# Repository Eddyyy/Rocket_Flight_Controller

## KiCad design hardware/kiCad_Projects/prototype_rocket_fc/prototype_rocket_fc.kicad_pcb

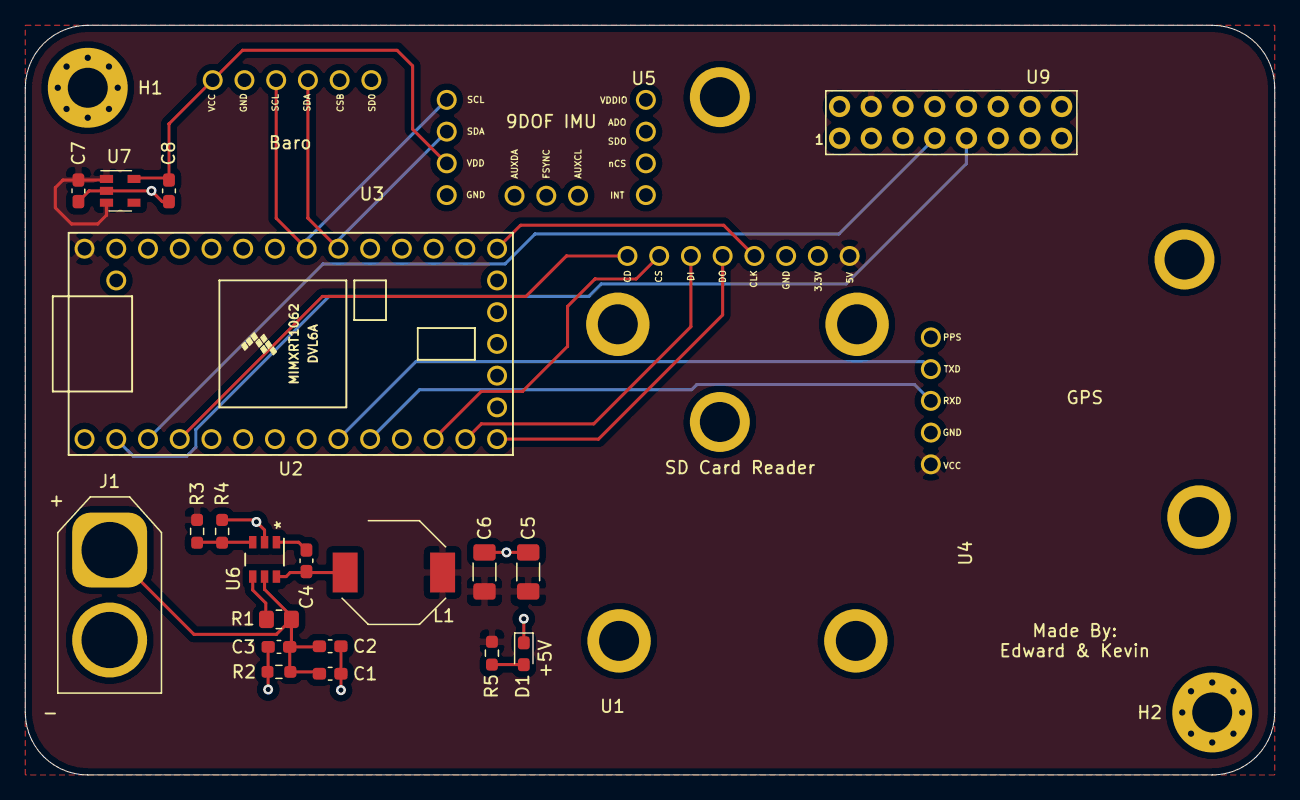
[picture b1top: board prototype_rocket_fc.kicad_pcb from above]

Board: 2 copper layers, 100.0 x 60.0 mm, 27 parts (1 on the bottom side), 20 nets.

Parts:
C1, C2: 10u; C_0603_1608Metric_Pad1.08x0.95mm_HandSolder
C3, C4: 100n; C_0603_1608Metric_Pad1.08x0.95mm_HandSolder
C5, C6: 10u; C_1206_3216Metric_Pad1.33x1.80mm_HandSolder
C7, C8: 1u; C_0603_1608Metric_Pad1.08x0.95mm_HandSolder
D1: LED; LED_0603_1608Metric_Pad1.05x0.95mm_HandSolder
H1, H2: MountingHole_Pad; MountingHole_3.2mm_M3_Pad_Via
J1: BATTERY_IN; AMASS_XT60-M_1x02_P7.20mm_Vertical
L1: 15u; L_Bourns-SRU8043
R1: 665k; R_0805_2012Metric_Pad1.20x1.40mm_HandSolder
R2: 200k; R_0603_1608Metric_Pad0.98x0.95mm_HandSolder
R3: 88.7k; R_0603_1608Metric_Pad0.98x0.95mm_HandSolder
R4: 22.1k; R_0603_1608Metric_Pad0.98x0.95mm_HandSolder
R5: 200; R_0603_1608Metric_Pad0.98x0.95mm_HandSolder
U1: SD_Card_Reader; RobotDyn_SD_Card_Reader
U2: Teensy4.0; Teensy40
U3: GY-BMP280
U4: TinyGPS++
U5: MPU9250_custom; MPU9250
U6: LMR50410XFDBVR
U7: MIC5504-3.3YM5; SOT-23-5
U8: RFD900x_Mech
U9: RFD900x_Pins

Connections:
+3V3: C8.1, U3.1, U5.3, U7.5
+5V: C5.1, C6.1, C7.1, L1.2, R3.1, R5.1, U1.1, U2.33, U4.5, U7.1, U7.3, U9.4
/CD: U1.8, U2.4
/CS: U1.7, U2.12
/MISO: U1.5, U2.14
/MOSI: U1.6, U2.13
/RX1: U2.2, U9.9
/RX2: U2.9, U4.2
/SCK: U1.4, U2.20
/SCL0: U2.26, U3.3, U5.1
/SDA0: U2.25, U3.4, U5.2
/TX1: U2.3, U9.7
/TX2: U2.10, U4.3
/battery_power_supply/CB: C4.2, U6.1
/battery_power_supply/EN: R1.2, U6.4
/battery_power_supply/FB: R3.2, R4.1, U6.3
/battery_power_supply/SW: C4.1, L1.1, U6.6
GND: C1.2, C2.2, C3.2, C5.2, C6.2, C7.2, C8.2, D1.1, H1.1, H2.1, J1.2, R2.2, R4.2, U1.3, U2.32, U3.2, U4.4, U5.4, U6.2, U7.2, U8.1, U9.1
unnamed: D1.2, R5.2
VCC: C1.1, C2.1, C3.1, J1.1, R1.1, R2.1, U6.5

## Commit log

2021-04-30 Setting up repositry
2021-04-30 writen simple hello world check
2021-05-02 Finish simple baro read
2021-05-04 ignore .vscsode
2021-05-04 Working on calc real temp and pres
2021-05-04 setup accelerometer reading
2021-05-04 printing accelerometer readings in CSV format
2021-05-04 added requisite .h and .cpp files
2021-05-07 fixed when data is being read, WIP:Mag values
2021-05-07 fixed mag values not reading (fml)
2021-05-10 GPS reading dev
2021-05-10 basic reading of GPS data
2021-05-10 Mostly working baro
2021-05-10 reading thrugh to serial using rfd
2021-05-10 Basic serial connection
2021-05-10 Basic GPS module readouts
2021-05-12 adding simple files
2021-05-12 Adding chrt stuff
2021-05-12 imu rtos test
2021-05-13 dodgy gps and working imu
2021-05-13 janky GPS thread should now work
2021-05-19 hardware files
2021-05-19 baro reading thread
2021-05-19 requisite library files
2021-05-19 buffering data and writing to SD card
2021-05-21 Added pause execution for SD card reader
2021-05-21 gerber files
2021-05-25 Sd card writing with millisecond time stamp working
2021-05-25 initial flight code code
2021-05-26 user defined start and stopping
2021-05-26 new gerber files
2021-05-26 RF Link works
2021-05-26 Updated hardware components inccluding RFD900x
2021-05-26 some formatting for serial out
2021-06-01 RFD version of pcb files
2021-06-08 #defining values for easier changes
2021-06-09 modified requirements
2021-06-09 Fixing ground not connected
2021-06-09 fixed gps #define
2021-06-11 graph GUI set up, open serial button may or may not work
2021-06-18 Starting iteration 1 pcbs
2021-06-21 prototype graphing
2021-06-21 data lines now single line
2021-06-21 added close serial
2021-06-21 feedback on button presses
2021-06-21 error check if sd card not opened
2021-06-21 removed writing to buffer and seperated all prints to own thread
2021-06-22 starting iteration 1 igniter circuit
2021-06-23 wrapped serial and file out with mutex
2021-06-23 seperate file for each data set
2021-06-23 declaring files as global
2021-09-20 Adding model prototype files
2021-09-27 Adding ekf functions
